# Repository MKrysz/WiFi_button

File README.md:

# WiFi_button
 
# V01 bugs:
 - wrong pin tied to ground / booting in programming mode is impossible
 - button is too small
 - no battery check needed (mcu works way longer than blue led)
 - make programming automatic (no boot jumpers and manual resets)

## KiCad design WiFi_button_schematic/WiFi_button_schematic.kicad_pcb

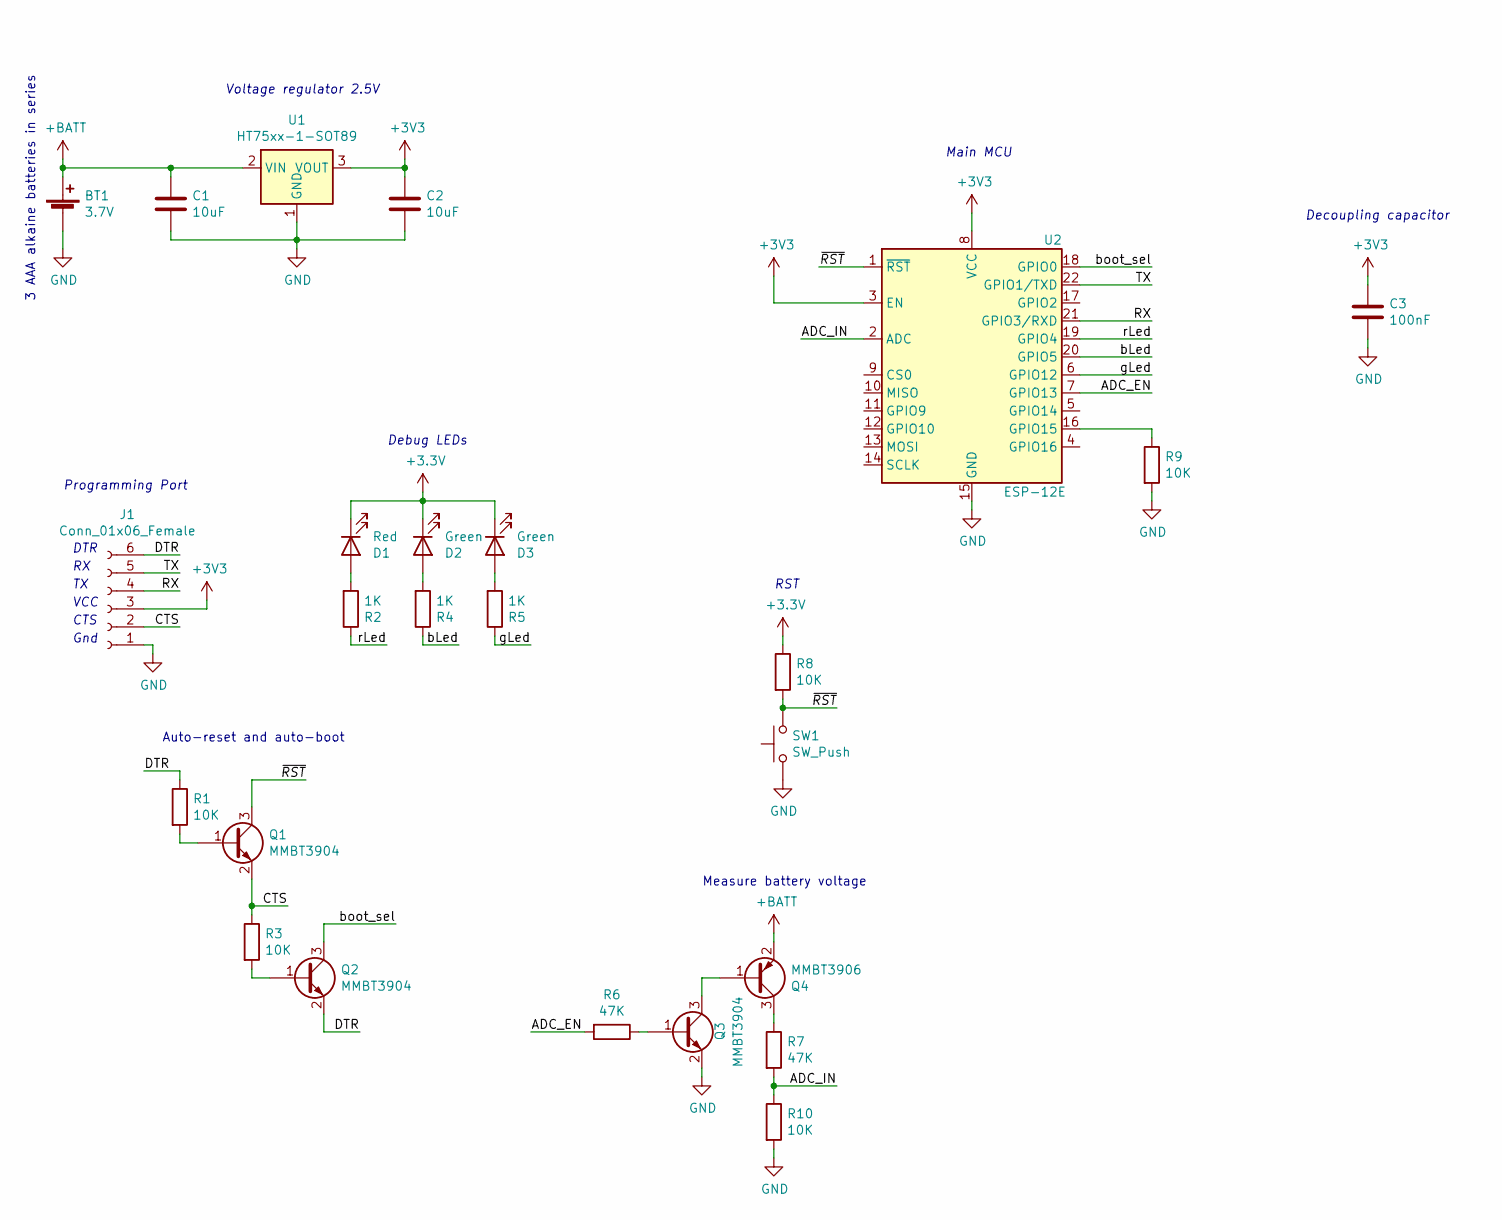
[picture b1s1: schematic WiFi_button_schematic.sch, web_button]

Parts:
BT1: 3.7V; PinHeader_1x02_P2.54mm_Vertical
C1, C2: 10uF; C_1206_3216Metric_Pad1.33x1.80mm_HandSolder
C3: 100nF; C_1206_3216Metric_Pad1.33x1.80mm_HandSolder
D1: Red; LED_1206_3216Metric_Pad1.42x1.75mm_HandSolder
D2, D3: Green; LED_1206_3216Metric_Pad1.42x1.75mm_HandSolder
J1: Conn_01x06_Female; PinHeader_1x06_P2.54mm_Vertical
Q1, Q2, Q3: MMBT3904; SOT-23_Handsoldering
Q4: MMBT3906; SOT-23_Handsoldering
R1, R3, R8, R9, R10: 10K; R_1206_3216Metric_Pad1.30x1.75mm_HandSolder
R2, R4, R5: 1K; R_1206_3216Metric_Pad1.30x1.75mm_HandSolder
R6, R7: 47K; R_1206_3216Metric_Pad1.30x1.75mm_HandSolder
SW1: SW_Push; sw_push_12_x_12_mm
U1: HT75xx-1-SOT89; SOT-89-3_Handsoldering
U2: ESP-12E

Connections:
+BATT: BT1.1 (+), C1.1, Q4.2 (E), U1.2 (VIN)
/ADC_EN: R6.2, U2.7 (GPIO13)
/ADC_IN: R7.2, R10.1, U2.2 (ADC)
/CTS: J1.2, Q1.2 (E), R3.1
/DTR: J1.6, Q2.2 (E), R1.1
/RX: J1.4, U2.21 (GPIO3/RXD)
/TX: J1.5, U2.22 (GPIO1/TXD)
/bLed: R4.1, U2.20 (GPIO5)
/boot_sel: Q2.3 (C), U2.18 (GPIO0)
/gLed: R5.1, U2.6 (GPIO12)
/rLed: R2.1, U2.19 (GPIO4)
/~RST: Q1.3 (C), R8.2, SW1.2, U2.1 (~RST)
GND: BT1.2 (-), C1.2, C2.2, C3.2, J1.1, Q3.2 (E), R9.2, R10.2, SW1.1, U1.1 (GND), U2.15 (GND)
unnamed: D1.2 (A), R2.2
unnamed: D2.2 (A), R4.2
unnamed: D3.2 (A), R5.2
unnamed: Q1.1 (B), R1.2
unnamed: Q2.1 (B), R3.2
unnamed: Q3.1 (B), R6.1
unnamed: Q3.3 (C), Q4.1 (B)
unnamed: Q4.3 (C), R7.1
unnamed: R9.1, U2.16 (GPIO15)

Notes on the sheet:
Gnd
Decoupling capacitor
Voltage regulator 2.5V
Programming Port
Debug LEDs
Main MCU
DTR
VCC
CTS
RST
3 AAA alkaine batteries in series
Auto-reset and auto-boot
Measure battery voltage

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
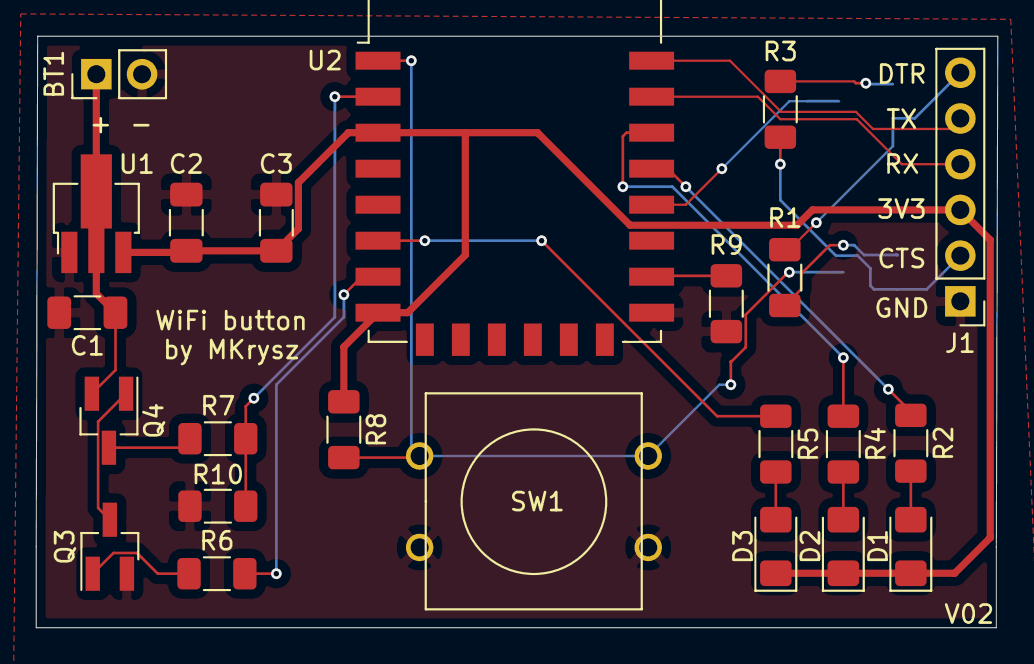
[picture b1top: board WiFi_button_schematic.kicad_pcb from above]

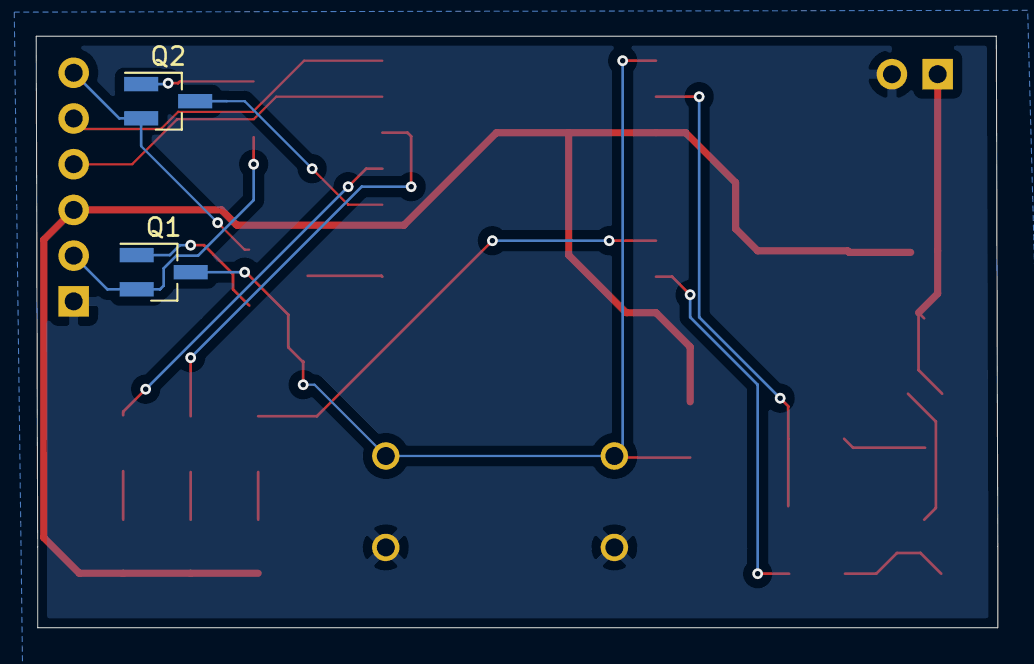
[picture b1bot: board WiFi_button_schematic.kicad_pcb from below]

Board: 2 copper layers, 53.4 x 32.9 mm, 25 parts (2 on the bottom side), 23 nets.

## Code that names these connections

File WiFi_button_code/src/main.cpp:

#include <Arduino.h>
#include <ESP8266WiFi.h>
#include <ESP8266HTTPClient.h>
#include <WiFiClient.h>
#include <stdio.h>


const int gled = 5;
const int bled = gled;
const int rled = 4;
const float vol_div = 0.1754386;
const int adc_en = 13;
const int adc_in = A0;
const char serverName[] = "http://raspberrypi.local:80";
const char WIFI_ssid[] = "Y'Ghatan";
const char WIFI_pass[] = "06094829";

int sendPOST_toWebCounter(const char exercise[32], int number);
int checkVoltage();
void warnLowVoltage();
void blink(uint8_t led, int times, int onTime = 300, int offTime = 300);
void turnOff();

void setup() {
  uint32 start_time = millis();
  pinMode(rled, OUTPUT);
  pinMode(bled, OUTPUT);
  pinMode(gled, OUTPUT);
  pinMode(adc_en, OUTPUT);
  digitalWrite(rled, HIGH);
  digitalWrite(bled, HIGH);
  digitalWrite(gled, HIGH);
  digitalWrite(adc_en, LOW);
  Serial.begin(115200);
  Serial.println("booting up...");
  WiFi.begin(WIFI_ssid, WIFI_pass);
  checkVoltage(); 
  int i = 50;
  while((!WiFi.isConnected())&&(i --> 0)){
    blink(bled, 1, 100, 100);
  }
  Serial.println(WiFi.SSID());
  Serial.println(WiFi.localIP());
  digitalWrite(bled, LOW);
  Serial.println("Sending query...");
  int queryRes = sendPOST_toWebCounter("Nadchwyt", 6);
  if (queryRes == 200)
  {
    Serial.println("Query send successfully");
    digitalWrite(bled, HIGH);
    digitalWrite(gled, LOW);
    delay(1000);
  }
  else
  {
    Serial.println("An error has occured during sending query");
    Serial.print("Code received : ");
    Serial.print(queryRes);
    Serial.println();
    digitalWrite(bled, HIGH);
    digitalWrite(rled, LOW);
    delay(10000);
  }
  
  Serial.println("shutting off...");
  Serial.print("Overall on duration = ");
  Serial.print(millis()-start_time);
  turnOff(); 
}



void loop() {
  // put your main code here, to run repeatedly:
}



int sendPOST_toWebCounter(const char exercise[32], int number) 
{
  char requestData[128];
  WiFiClient client;
  HTTPClient http;
  sprintf(requestData, "%s_number=%u&%s=%%2B", exercise, number, exercise);
  http.begin(client, serverName);
  http.addHeader("Content-Type", "application/x-www-form-urlencoded");
  int httpResponse = http.POST(requestData);
  http.end();
  return httpResponse;
}

/*
@brief checks voltage level of the battery and warns user if the battery is low
@return 0 if battery is fine, 1 if battery is low
*/
int checkVoltage() 
{
  const float lowBatThreshold = 2.5;
  digitalWrite(adc_en, HIGH);
  int rawRead = analogRead(adc_in);
  float readVoltage = (((float)rawRead/1023.00)*(1/vol_div));
  // Serial.println(rawRead);
  Serial.print("Uzas = ");
  Serial.print(readVoltage);
  Serial.println('V');
  if(readVoltage < lowBatThreshold){
    warnLowVoltage();
    return 1;
  }
  return 0;
}

void warnLowVoltage() 
{
  blink(rled, 3);
}

void blink(uint8_t led, int times, int onTime, int offTime)
{
  for(int i = 0; i<times; i++){
    digitalWrite(led, LOW);
    delay(onTime);
    digitalWrite(led, HIGH);
    delay(offTime);
  }
}


void turnOff()
{
  digitalWrite(rled, HIGH);
  digitalWrite(bled, HIGH);
  digitalWrite(gled, HIGH);
  delay(10);
  ESP.deepSleep(0);
}

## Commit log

2021-10-02 Added platformio project with working deep sleep
2021-10-02 Working prototype
2021-10-03 Created schematic
2021-10-03 Commented verbose prints, and added prints measuring boot times
2021-10-04 Version v01 finished
2021-10-04 Using DNS instead of IP
2021-10-04 Removed Serial and added warning when server didn't response with OK
2021-10-04 Changed capacitors' and resistors' sizes to 1206
2021-10-07 Added on-btn and reduced heavily idle current
2021-11-02 Project is now less complicated
2021-12-01 V02 of schematic finished
2021-12-01 Added circuit for measuring battery voltage
2021-12-04 Version v02
